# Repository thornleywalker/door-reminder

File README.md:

# Door Reminder Project

This is the repository for the Door Reminder project.
Schematics and board layout are in hardware folder.
Board software and app files are in software folder.

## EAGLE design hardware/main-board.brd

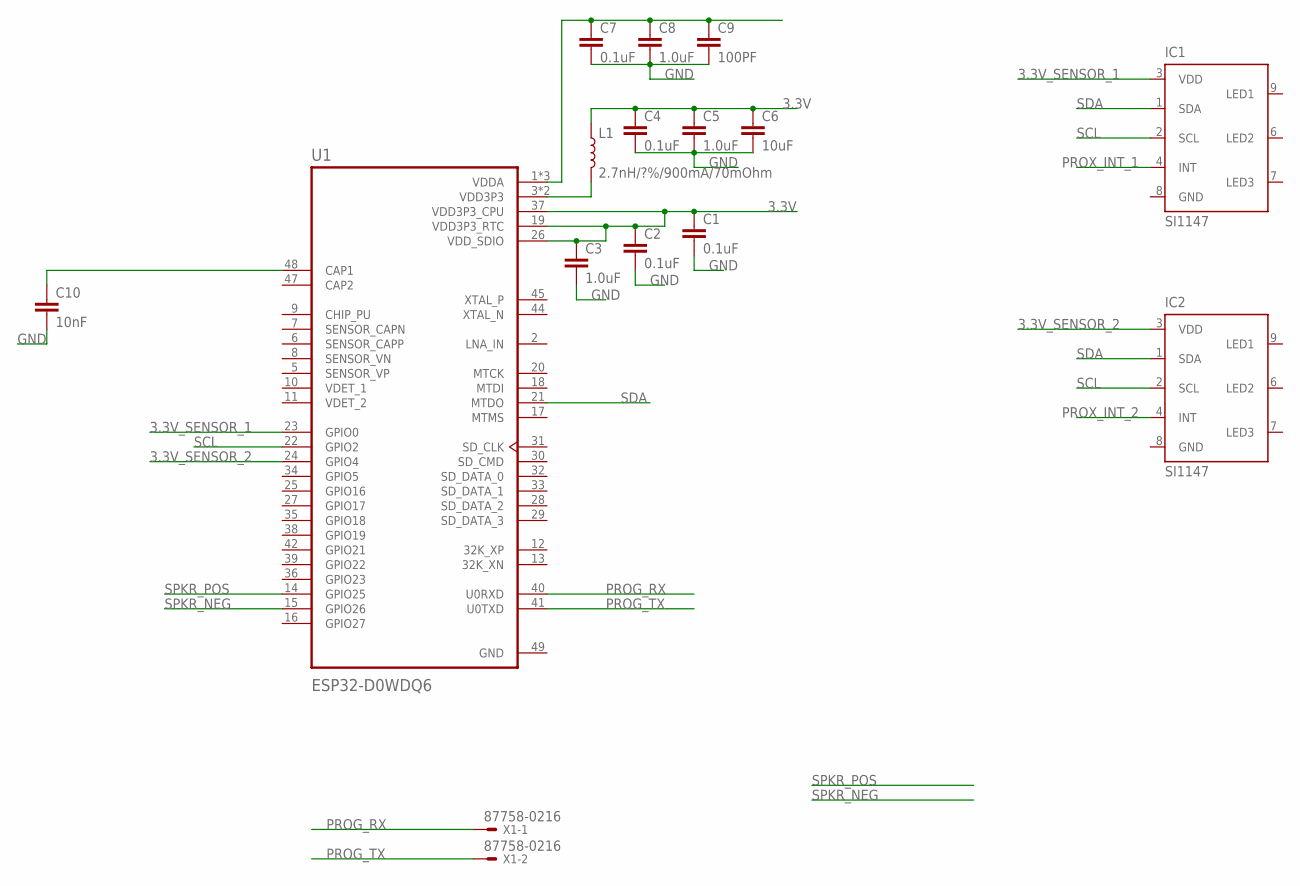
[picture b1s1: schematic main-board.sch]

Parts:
C1, C2: 0.1uF; 0603
C3: 1.0uF; 0603
C4, C7: 0.1uF; 0402
C5, C8: 1.0uF; 0402
C6: 10uF; 0805
C9: 100PF; 0402
C10: 10nF; 0603
IC1, IC2: SI1147; QFN-10
L1: 2.7nH/?%/900mA/70mOhm; 0402-TIGHT
U1: ESP32-D0WDQ6; QFN35P500X500X90-49N
X1: 87758-0216

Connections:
3.3V: C1.1, C2.1, C3.1, C4.1, C5.1, C6.1, L1.1, U1.19 (VDD3P3_RTC), U1.26 (VDD_SDIO), U1.37 (VDD3P3_CPU)
3.3V_SENSOR_1: IC1.3 (VDD), U1.23 (GPIO0)
3.3V_SENSOR_2: IC2.3 (VDD), U1.24 (GPIO4)
GND: C1.2, C2.2, C3.2, C4.2, C5.2, C6.2, C7.2, C8.2, C9.2, C10.2, IC1.8 (GND), IC2.8 (GND), U1.49 (GND)
unnamed: C10.1, U1.48 (CAP1)
unnamed: C7.1, C8.1, C9.1, U1.1 (VDDA), U1.43 (VDDA), U1.46 (VDDA)
unnamed: L1.2, U1.3 (VDD3P3), U1.4 (VDD3P3)
PROG_RX: U1.40 (U0RXD), X1.1
PROG_TX: U1.41 (U0TXD), X1.2
PROX_INT_1: IC1.4 (INT)
PROX_INT_2: IC2.4 (INT)
SCL: IC1.2 (SCL), IC2.2 (SCL), U1.22 (GPIO2)
SDA: IC1.1 (SDA), IC2.1 (SDA), U1.21 (MTDO)
SPKR_NEG: U1.15 (GPIO26)
SPKR_POS: U1.14 (GPIO25)

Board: 2 copper layers, 15 parts (0 on the bottom side), 11 nets, no tracks yet.

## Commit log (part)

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2020-07-28 created empty hardware files
2020-07-28 create empty flutter app project
2020-07-28 created empty board software project
2020-07-28 added useful pdfs, EAGLE part libraries
2020-07-28 added programming guide link
2020-07-28 reorganize hardware folder
2020-07-31 added build folder to .gitignore
2020-07-31 added tx/rx pins for programming
2020-08-01 vscode updates
2020-08-01 created singleton class with basic functions
2020-08-01 created database class for interfacing with firebase
2020-08-01 created wifi class for interfacing with esp board wifi connection
2020-08-01 removed default code
2020-08-01 renamed from hello_world to door_reminder
2020-08-01 simple update
2020-08-02 created bluetooth interface files and associated singleton structs
2020-08-03 begin work on app, joining with firebase
2020-08-03 adding firebase to pubspec
2020-08-04 ios generated files
2020-08-04 change to build gradle
2020-08-04 ios updates
2020-08-04 creating structure for login/signup
2020-08-04 create account and login functional
2020-08-04 moved auth to singleton
2020-08-04 added empty hamburger and account menu files
2020-08-04 added bodies to menu generators
2020-08-04 added basic routes
2020-08-04 updated signout method, created password confirmation to signup
2020-08-04 added elses to some ifs
2020-08-04 initial database commit
2020-08-05 Changed app name to Doorsi instead of door_reminder
2020-08-05 removed unnecesary code
2020-08-05 can add reminders to database
2020-08-08 created add device basic logic
2020-08-19 added flutter_blue to dependencies
2020-08-19 updated firebase dependencies and associated code
2020-08-19 Revert "updated firebase dependencies and associated code"
    This reverts commit 6e0114d392f5e5a202b2a5108d77227b87eaaf9f.
2020-08-19 added firebase messaging
2020-08-19 updated dependencies and associated files/functions
    updated all firebase dependencies to most recent version as to be able to use firebase_messaging in it's most recent form. fixed files so app loads
2020-08-19 added push notification ability
2020-08-19 added devices route
2020-08-19 added button to devices
2020-08-19 added user form to New Reminder dialog
2020-08-20 added reminder list getter to singleton
2020-08-20 somefin
2020-08-20 Revert "Merge branch 'reminders'"
    This reverts commit 1b83178d14e6f95aa227b9d68e03d1689b74a39e, reversing
    changes made to 34500aca34faccd70657f6144c022982e7189391.
2020-08-20 Revert "Merge branch 'devices-route'"
    This reverts commit 64f170af6845e7ce557e234ddd486a701e125dbb, reversing
    changes made to 1b83178d14e6f95aa227b9d68e03d1689b74a39e.
2020-08-21 made home screen display list of all reminders
    Singleton now gets all reminders from database when building home screen.
2020-08-22 added list title to home screen
2020-08-22 remove reminder list when logging out
2020-08-22 added ability to delete reminders from in app
    singleton removes reminder from database, and remidners list
    home page refreshes to remove from displayed list
2020-08-25 reconfigure esp-idf to work with vscode
2020-08-25 more vscode stuff
2020-11-09 added clang format
2020-11-30 added nvs storage
2020-11-30 rename database to database proxy
2020-11-30 misc changes
2020-12-12 more stuff
2020-12-13 refamiliarizing
2020-12-13 gitignore updated
2020-12-13 update gitignores
2020-12-13 editing gitignores
2020-12-13 update device todo
2020-12-13 added esp idf to include path
2020-12-13 changing gitignore
2020-12-13 added esp-idf as submodule
2020-12-13 Create esp-idf
2020-12-13 changed file asociations
2020-12-14 rename singleton to data cache
2020-12-14 added basic icon thoughts
2020-12-14 changed singleton to data cache
2020-12-15 added user parsing
2020-12-15 add file association
2020-12-15 esp-idf change
2020-12-15 updated to have new database structure
2020-12-15 testing different colors
2020-12-17 ignore open word documents
2020-12-17 rename image project
2020-12-17 reorganize files into services, objects, screens , and widgets
2020-12-18 changed data cache file name
2020-12-18 created device class
2020-12-18 updated reminder builder to user new db structure
2020-12-21 rearranged file structure
2020-12-21 added onComplete callback
2020-12-21 implemented basic home screen functionality
2020-12-21 added parameter requirements
2020-12-21 auto update
2020-12-21 reworked database functions to use new structure
2020-12-21 Moved notifications to separate file, made singleton
2020-12-21 updated to send notification to user on flag
2020-12-23 builds project, opens putty if successful
2020-12-23 minor spelling changes
2020-12-23 added init function and removed excess code
2020-12-23 setup gpio pin for testing
2020-12-23 fixed spelling, created init function
2020-12-23 created nvs update function
2020-12-23 added all source files
2020-12-23 setup basic test run
2020-12-23 added init function
2020-12-23 updated to new db structure
2020-12-23 fixed not being able to find http client
2020-12-23 put monitor in the existing terminal
2020-12-23 finished singleton to data cache change
2020-12-23 added wifi connection check
2020-12-23 added automated notification test
2020-12-23 changed tag to identify project logs
2020-12-23 fixed uid length
2020-12-23 fixed logging messages
2020-12-23 fixed json parsing and flag setting
2020-12-23 changed to set flags only on interrupt
2020-12-23 added going and coming isr's
2020-12-24 added sensor section, cleared db proxy
2020-12-24 changed infinite loop to basic counter
2020-12-24 figured out which pins were which
2020-12-24 added separate task to handle notifications
2020-12-24 gave reninder setting it's own http client
2020-12-24 moved sensor init to after wifi and db proxy
2020-12-24 removed finished tasks
2020-12-24 commenting
2020-12-24 Bump date-and-time from 0.14.1 to 0.14.2 in /software/backend/functions
    Bumps [date-and-time](https://github.com/knowledgecode/date-and-time) from 0.14.1 to 0.14.2.
    - [Release notes](https://github.com/knowledgecode/date-and-time/releases)
    - [Commits](https://github.com/knowledgecode/date-and-time/compare/v0.14.1...v0.14.2)
2021-03-09 Auto updates
2021-03-09 Created diagram
2021-03-09 Created si115x library
2021-03-09 began i2c for si115x's
2021-04-26 si115x
2021-05-04 Added macros
2021-05-04 added basic fns
2021-05-05 added reference sheet
2021-05-05 added comments and references
2021-05-05 implemented fns
2021-05-05 auto-updates
2021-05-07 added storage structs
2021-05-07 added i2c configuration to init
2021-05-07 changed to use si115x.h
2021-05-11 Bump lodash from 4.17.20 to 4.17.21 in /software/backend/functions
    Bumps [lodash](https://github.com/lodash/lodash) from 4.17.20 to 4.17.21.
    - [Release notes](https://github.com/lodash/lodash/releases)
    - [Commits](https://github.com/lodash/lodash/compare/4.17.20...4.17.21)
2021-11-13 initial rust commit
2021-11-15 fleshed out rust
2021-12-05 added most basic concepts
2021-12-11 initial rust attempt
2021-12-11 Added programming file to attempt programming from Windows
2022-03-18 general updates
2022-03-28 Bump minimist from 1.2.5 to 1.2.6 in /software/backend/functions
    Bumps [minimist](https://github.com/substack/minimist) from 1.2.5 to 1.2.6.
    - [Release notes](https://github.com/substack/minimist/releases)
    - [Commits](https://github.com/substack/minimist/compare/1.2.5...1.2.6)
    ---
    updated-dependencies:
    - dependency-name: minimist
2022-06-02 Bump protobufjs from 6.10.2 to 6.11.3 in /software/backend/functions
    Bumps [protobufjs](https://github.com/protobufjs/protobuf.js) from 6.10.2 to 6.11.3.
    - [Release notes](https://github.com/protobufjs/protobuf.js/releases)
    - [Changelog](https://github.com/protobufjs/protobuf.js/blob/v6.11.3/CHANGELOG.md)
    - [Commits](https://github.com/protobufjs/protobuf.js/compare/v6.10.2...v6.11.3)
    ---
    updated-dependencies:
2022-06-06 Bump crossbeam-utils from 0.8.5 to 0.8.8 in /software/rust-esp
    Bumps [crossbeam-utils](https://github.com/crossbeam-rs/crossbeam) from 0.8.5 to 0.8.8.
    - [Release notes](https://github.com/crossbeam-rs/crossbeam/releases)
    - [Changelog](https://github.com/crossbeam-rs/crossbeam/blob/master/CHANGELOG.md)
    - [Commits](https://github.com/crossbeam-rs/crossbeam/compare/crossbeam-utils-0.8.5...crossbeam-utils-0.8.8)
    ---
    updated-dependencies:
2022-06-06 Bump regex from 1.5.4 to 1.5.6 in /software/rust-esp
    Bumps [regex](https://github.com/rust-lang/regex) from 1.5.4 to 1.5.6.
    - [Release notes](https://github.com/rust-lang/regex/releases)
    - [Changelog](https://github.com/rust-lang/regex/blob/master/CHANGELOG.md)
    - [Commits](https://github.com/rust-lang/regex/compare/1.5.4...1.5.6)
    ---
    updated-dependencies:
2022-06-17 Bump thread_local from 1.1.3 to 1.1.4 in /software/rust-esp
    Bumps [thread_local](https://github.com/Amanieu/thread_local-rs) from 1.1.3 to 1.1.4.
    - [Release notes](https://github.com/Amanieu/thread_local-rs/releases)
    - [Commits](https://github.com/Amanieu/thread_local-rs/compare/v1.1.3...1.1.4)
    ---
    updated-dependencies:
    - dependency-name: thread_local
2022-06-25 Bump node-fetch from 2.6.1 to 2.6.7 in /software/backend/functions
    Bumps [node-fetch](https://github.com/node-fetch/node-fetch) from 2.6.1 to 2.6.7.
    - [Release notes](https://github.com/node-fetch/node-fetch/releases)
    - [Commits](https://github.com/node-fetch/node-fetch/compare/v2.6.1...v2.6.7)
    ---
    updated-dependencies:
    - dependency-name: node-fetch
2022-11-10 Bump minimatch from 3.0.4 to 3.1.2 in /software/backend/functions
    Bumps [minimatch](https://github.com/isaacs/minimatch) from 3.0.4 to 3.1.2.
    - [Release notes](https://github.com/isaacs/minimatch/releases)
    - [Commits](https://github.com/isaacs/minimatch/compare/v3.0.4...v3.1.2)
    ---
    updated-dependencies:
    - dependency-name: minimatch
2022-12-08 Bump qs and express in /software/backend/functions
    Bumps [qs](https://github.com/ljharb/qs) and [express](https://github.com/expressjs/express). These dependencies needed to be updated together.
    Updates `qs` from 6.7.0 to 6.11.0
    - [Release notes](https://github.com/ljharb/qs/releases)
    - [Changelog](https://github.com/ljharb/qs/blob/main/CHANGELOG.md)
    - [Commits](https://github.com/ljharb/qs/compare/v6.7.0...v6.11.0)
    Updates `express` from 4.17.1 to 4.18.2
2022-12-13 Bump express from 4.17.1 to 4.18.2 in /software/backend/functions
    Bumps [express](https://github.com/expressjs/express) from 4.17.1 to 4.18.2.
    - [Release notes](https://github.com/expressjs/express/releases)
    - [Changelog](https://github.com/expressjs/express/blob/master/History.md)
    - [Commits](https://github.com/expressjs/express/compare/4.17.1...4.18.2)
    ---
    updated-dependencies:
2023-01-10 Bump jsonwebtoken and firebase-admin in /software/backend/functions
    Bumps [jsonwebtoken](https://github.com/auth0/node-jsonwebtoken) to 9.0.0 and updates ancestor dependency [firebase-admin](https://github.com/firebase/firebase-admin-node). These dependencies need to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
    Updates `jsonwebtoken` from 8.5.1 to 9.0.0
    - [Release notes](https://github.com/auth0/node-jsonwebtoken/releases)
    - [Changelog](https://github.com/auth0/node-jsonwebtoken/blob/master/CHANGELOG.md)
    - [Commits](https://github.com/auth0/node-jsonwebtoken/compare/v8.5.1...v9.0.0)
    Updates `firebase-admin` from 9.4.2 to 11.4.1
2023-01-20 Bump bumpalo from 3.8.0 to 3.12.0 in /software/rust-esp
    Bumps [bumpalo](https://github.com/fitzgen/bumpalo) from 3.8.0 to 3.12.0.
    - [Release notes](https://github.com/fitzgen/bumpalo/releases)
    - [Changelog](https://github.com/fitzgen/bumpalo/blob/main/CHANGELOG.md)
    - [Commits](https://github.com/fitzgen/bumpalo/compare/3.8.0...3.12.0)
    ---
    updated-dependencies:

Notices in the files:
parts and their libraries:
SparkFun-Capacitors: Licensing: Creative Commons ShareAlike 4.0 International - https://creativecommons.org/licenses/by-sa/4.0
